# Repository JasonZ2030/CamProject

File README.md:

# Underwater Fishing Camera

## Introduction

As a shore angler, I've spent countless hours casting my line, waiting for bites that never came. The frustrating reality? I often had no idea if there were even any fish where I was casting. It didn't matter how good my lure was or how expensive my bait – if the fish weren't there, I wasn't catching anything.

Unlike anglers with boats who can afford expensive sonar fishfinders, I needed a budget-friendly solution that would work from the shore. That's when the idea hit me: why not create a small underwater camera that I could attach to my fishing line? This way, I could scout locations before wasting time fishing in empty water.

## Photos
<div style="display: flex; justify-content: space-around; margin: 20px 0;">

</div>

## Why ESP32-CAM?

The ESP32-CAM module was the perfect choice for this project. Its compact size makes it ideal for attaching to a fishing line without adding too much weight or bulk that would interfere with casting. The module is also incredibly easy to program, with built-in WiFi capabilities that allow real-time video streaming directly to my phone.

Compared to other camera solutions, the ESP32-CAM offered the best balance of:
- **Size**: Small enough to attach to fishing gear
- **Cost**: Affordable for a DIY project
- **Functionality**: Built-in camera and WiFi in one module
- **Ease of use**: Well-documented and beginner-friendly

<div style="display: flex; justify-content: space-around; margin: 20px 0;">

</div>

### Key Features
- Automatic recording triggered by water submersion
- Waterproof housing rated for freshwater fishing depths
- External power button (no need to open case)
- Removable battery compartment for quick swaps
- Compact design attachable to fishing line

## Design Challenges & Solutions

Building this underwater camera presented three major challenges that required creative engineering solutions:

### Challenge 1: Power Supply

The ESP32-CAM requires a stable 5-volt power supply, but standard batteries don't provide this exact voltage. I needed a compact, affordable power solution that could fit inside a waterproof housing.

**Solution: Custom PCB with Voltage Regulation**

I taught myself KiCAD and designed a custom printed circuit board to solve this problem. The PCB design included:
- A socket for a standard 9V battery (the most cost-effective option)
- An integrated voltage converter to step down from 9V to the required 5V
- A soldered outlet to securely attach the 9V battery
- Direct connection to the ESP32-CAM module

This custom board became the backbone of the entire system, efficiently powering the camera while keeping costs low.

<div style="display: flex; justify-content: space-around; margin: 20px 0;">

</div>
<div>

</div>
  
### Challenge 2: Waterproof Control Interface

Opening a watertight case every time I needed to power on the camera or start recording would be impractical and risk water damage. I needed external controls that maintained the waterproof seal.

**Solution: Waterproof Button and Water-Sensing Trigger**

I used a clear PVC pipe as the main housing, cut to the appropriate length with caps on both ends. For the control interface:

**Power Button:**
- Created a groove in one end cap for a button soldered directly to the PCB
- Applied a silicon coating over the button for waterproofing
- Applied a layer of rubber on top of the button 
- Added an outer cap that compressed the rubber and with an opening that allows the button to be pressed while maintaining the seal
- This allows powering the camera on/off without opening the case

**Automatic Recording Trigger:**
- Installed a steel pin that protrudes through the case (fully waterproofed)
- Connected the pin to the ESP32-CAM's input pins via the PCB
- When submerged, water conductivity creates a small current between the pin and ground
- The ESP32 detects this current and automatically starts recording
- This eliminates the need for manual recording activation once underwater

<div>

</div>

<div>

</div>

### Challenge 3: Battery Access and Replacement

While the main housing needed to remain sealed during use, I still needed a way to easily replace the 9V battery when it ran out, without compromising the waterproof integrity of the camera compartment.

**Solution: Screw-On Battery Compartment**

On the opposite end from the control button, I designed a removable battery compartment:
- Attached a tubular screw mechanism to the main PVC pipe
- Added a separate end cap that screws onto this mechanism
- Applied waterproof sealant to the threads for a watertight seal
- Inside this compartment, I installed the wiring and soldered the 9V battery socket
- The compartment can be unscrewed for battery replacement, then securely resealed

This design allows quick battery swaps without exposing the sensitive electronics in the main camera housing.

<div>
  
</div>

## Version 1: Proof of Concept

The first version wasn't pretty, but it worked. It was proof that the idea could be made. We had a waterproof underwater camera that could be attached to a fishing line, powered by an affordable battery system, and controlled without opening the case. While the aesthetics and refinement would come later, V1 successfully demonstrated that I could scout fishing spots from shore without expensive equipment.

<div style="display: flex; justify-content: space-around; margin: 20px 0;">
  
</div>

## Future Improvements

### Weight Distribution & Buoyancy
The camera doesn't balance well underwater because the heavy battery pulls it to one side, and air gets trapped unevenly in the case. Future versions will move parts around and balance the weight better so it floats straight.

### Live WiFi Video Streaming
Add live video streaming to a phone so I can see what's underwater in real-time instead of watching recorded footage later. This might need changes to how the camera is set up to get the WiFi signal working through water.

### Reverse-Facing Camera
Flip the camera around so it points backward. This way I can watch my lure as I reel it in and see how fish react to it, which helps me figure out what makes them bite.

### Size & Weight Reduction
Make the whole thing smaller and lighter by redesigning the circuit board to be more compact, switching to lighter batteries, and using a thinner case. This will make it easier to cast and attach to my fishing line.
## Contributing

If you are interested in improving the design or have suggestions, feel free to open an issue or submit a pull request!

## Contact

**Name**: Jason Zhang

**Email**: jason.zhang.duidui@gmail.com

---

*Built with passion for fishing and engineering*

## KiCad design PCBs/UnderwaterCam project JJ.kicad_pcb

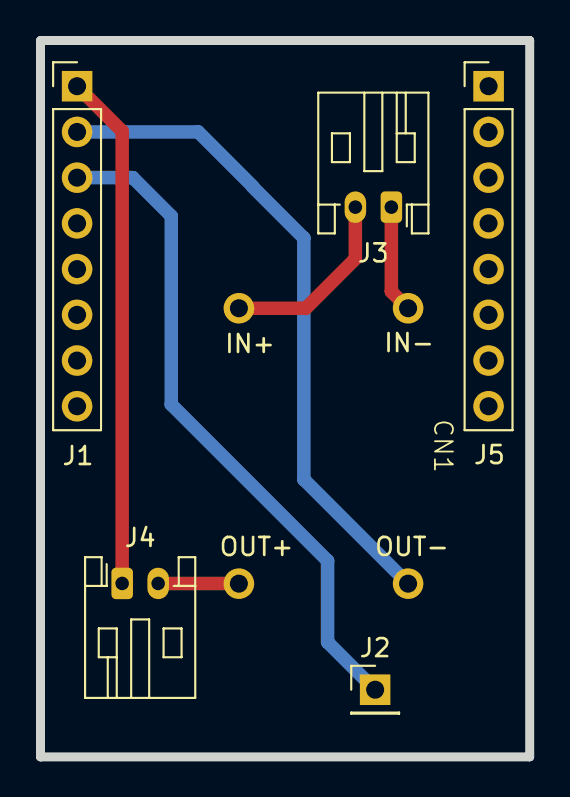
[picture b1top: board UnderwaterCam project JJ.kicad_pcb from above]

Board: 2 copper layers, 27.2 x 39.8 mm, 6 parts (0 on the bottom side), 5 nets.

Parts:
CN1: PowerSupplyConn
J1, J5: Conn_01x08; PinHeader_1x08_P2.54mm_Vertical
J2: Touch1; PinHeader_1x01_P2.54mm_Vertical
J3, J4: Conn_01x02; JST_PH_S2B-PH-K_1x02_P2.00mm_Horizontal

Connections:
unnamed: CN1.3 (IN+), J1.3, J2.1, J3.2
unnamed: CN1.1 (IN-), J3.1
unnamed: CN1.4 (OUT+), J4.2
unnamed: CN1.2 (OUT-), J1.2
unnamed: J1.1, J4.1

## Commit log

2023-11-25 Create CSS
    CSS for my html
2023-11-25 Update CSS
2025-10-23 Create placeholder
2025-10-23 Create placeholder
2025-10-26 Add initial content to READMEAUTO.md
2025-10-26 Convert README from HTML to Markdown
    Converted HTML content to Markdown format and added navigation section.
2025-10-30 Revise README for Underwater Fishing Camera project
    Updated the README to reflect the new project focus on an underwater fishing camera, including sections on introduction, design challenges, and solutions.
2025-11-01 Enhance README with key features and future plans
    Added key features and future improvements sections to the README.
2025-11-01 Create placholder
2025-11-01 Enhance README with project photos and details
    Added photos and descriptions for the underwater camera project, including features, challenges, and proof of concept.

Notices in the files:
PCBs/UnderwaterCam project JJ.kicad_pcb:
creativecommons.org/licenses/by/4.0
License: CC BY 4.0
